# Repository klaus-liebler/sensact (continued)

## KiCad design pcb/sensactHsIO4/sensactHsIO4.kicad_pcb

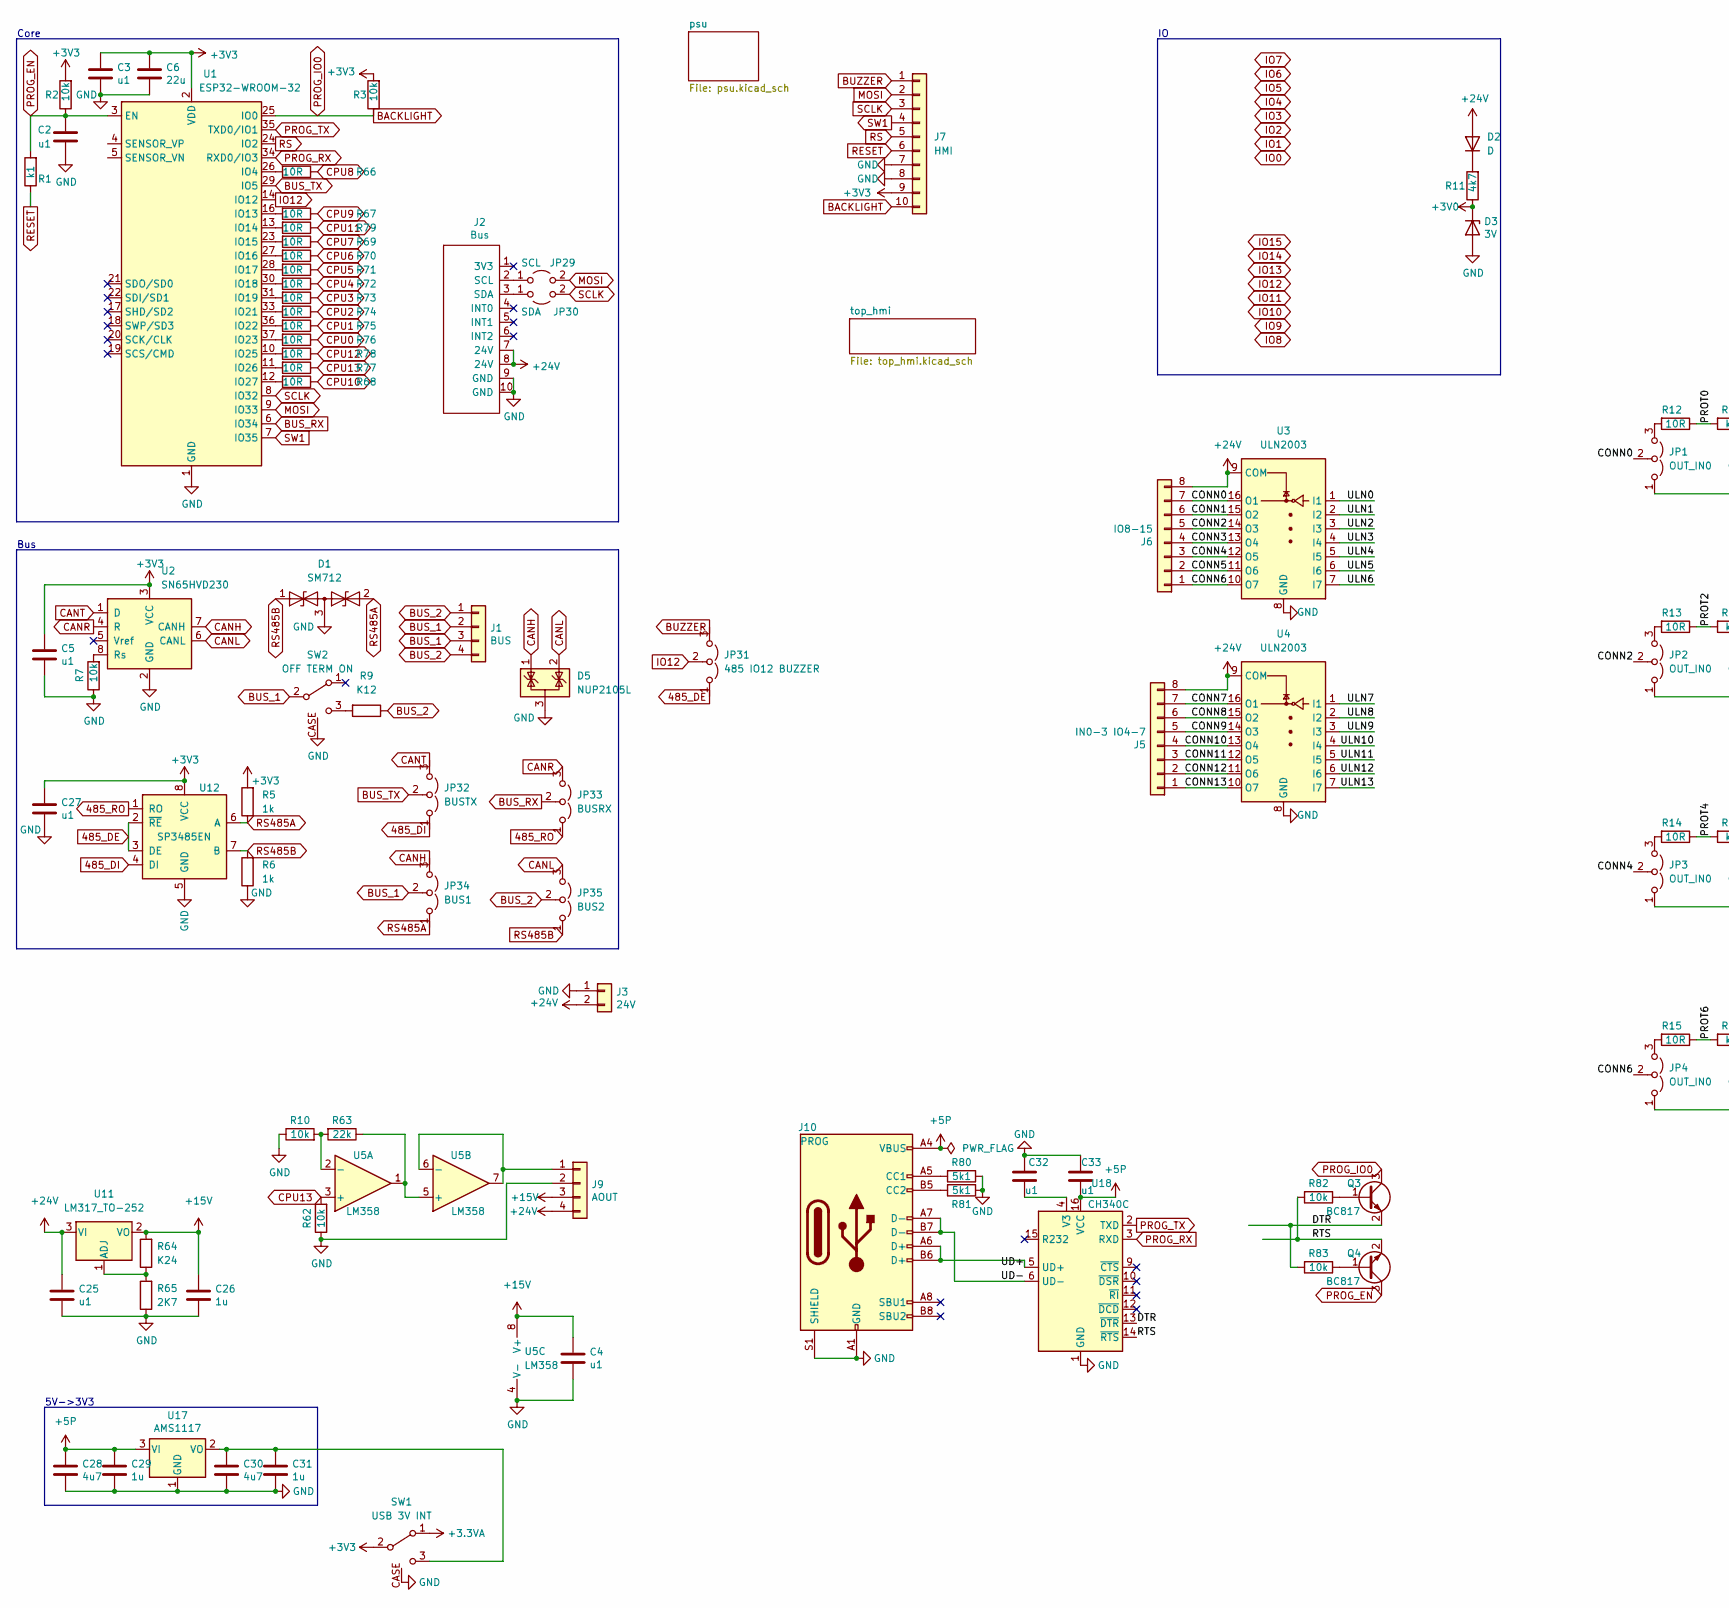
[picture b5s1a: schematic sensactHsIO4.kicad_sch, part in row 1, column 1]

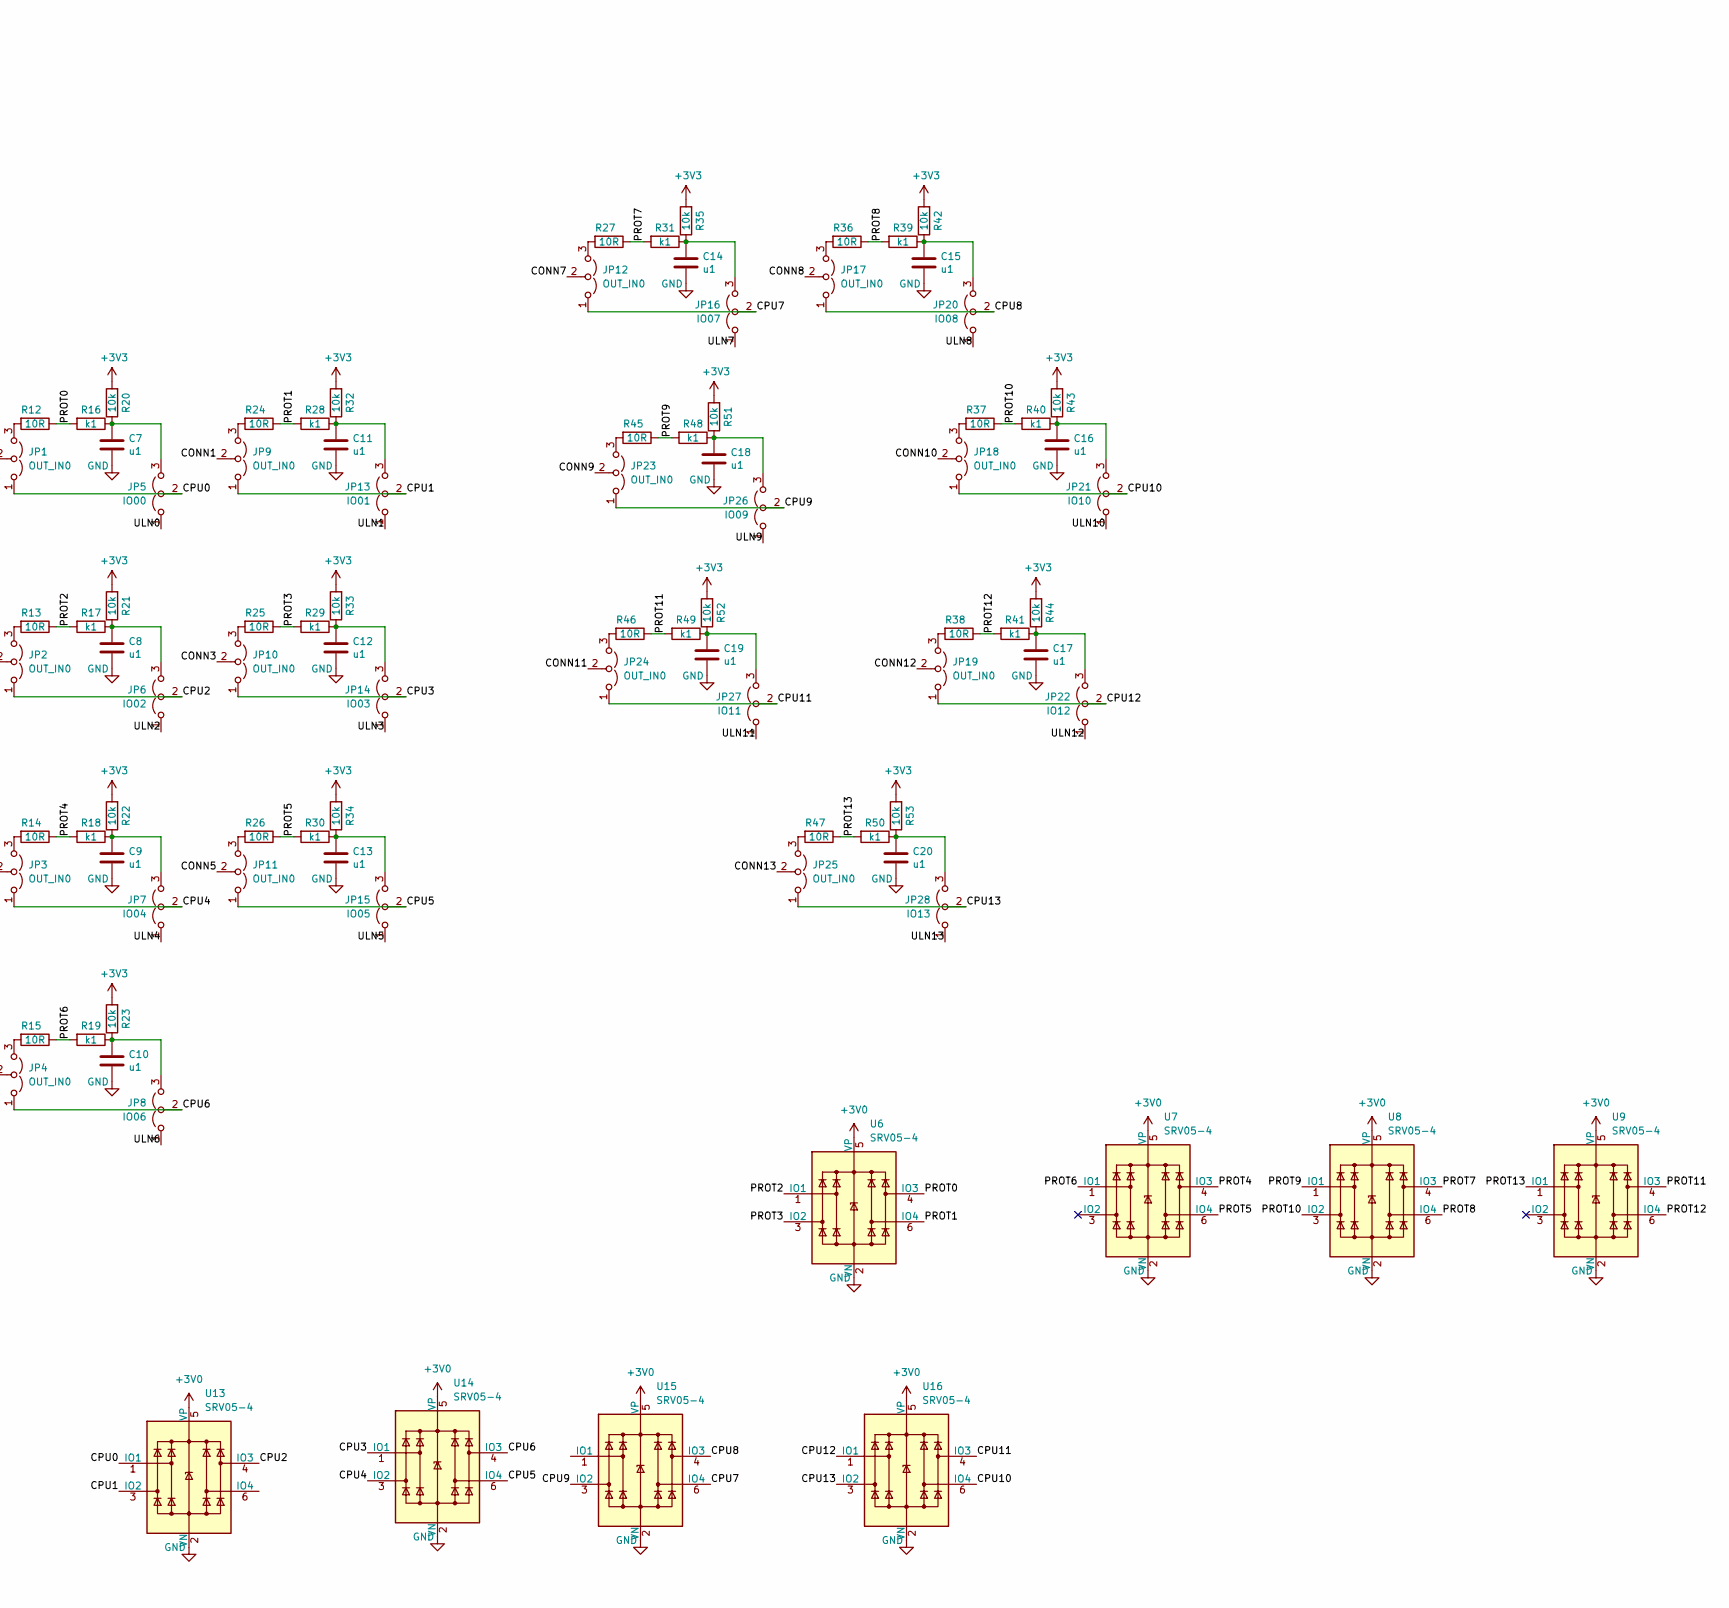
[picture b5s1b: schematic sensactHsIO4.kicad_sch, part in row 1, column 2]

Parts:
C2, C3, C7, C8, C9, C10, C11, C12, C13, C14, C15, C16, C17, C18, C19, C20: u1; C_0603_1608Metric
C4, C5, C25, C27, C32, C33: u1; C_0402_1005Metric
C6: 22u; C_0603_1608Metric
C26: 1u; C_0402_1005Metric
C28: 4u7; C_0603_1608Metric
C29: 1u; C_0603_1608Metric
C30: 4u7; C_0805_2012Metric_Pad1.18x1.45mm_HandSolder
C31: 1u; C_0805_2012Metric_Pad1.18x1.45mm_HandSolder
D1: SM712; SOT-23_Handsoldering
D2: D; D_SOD-123
D3: 3V; D_SOD-123
D5: NUP2105L; SOT-23_Handsoldering
J1: BUS; PhoenixContact_MC_1,5_4-G-3.5_1x04_P3.50mm_Horizontal
J2: Bus; IDC-Header_2x05_P2.54mm_Horizontal_tightCrtYd
J3: 24V; PhoenixContact_MC_1,5_2-G-3.5_1x02_P3.50mm_Horizontal
J5: IN0-3 IO4-7; PhoenixContact_MC_0,5_8-G-2.5_1x08_P2.50mm_Horizontal
J6: IO8-15; PhoenixContact_MC_0,5_8-G-2.5_1x08_P2.50mm_Horizontal
J7: HMI; Hirose_FH12-10S-0.5SH_1x10-1MP_P0.50mm_Horizontal
J9: AOUT; JST_XH_B4B-XH-A_1x04_P2.50mm_Vertical
J10: PROG; USB-C-HANBO-MC-307_C961709
JP1, JP2, JP3, JP4, JP9, JP10, JP11, JP12, JP17, JP18, JP19, JP23, JP24, JP25: OUT_IN0; SolderJumper-3_P1.3mm_Open_RoundedPad1.0x1.5mm
JP5: IO00; SolderJumper-3_P1.3mm_Open_RoundedPad1.0x1.5mm
JP6: IO02; SolderJumper-3_P1.3mm_Open_RoundedPad1.0x1.5mm
JP7: IO04; SolderJumper-3_P1.3mm_Open_RoundedPad1.0x1.5mm
JP8: IO06; SolderJumper-3_P1.3mm_Open_RoundedPad1.0x1.5mm
JP13: IO01; SolderJumper-3_P1.3mm_Open_RoundedPad1.0x1.5mm
JP14: IO03; SolderJumper-3_P1.3mm_Open_RoundedPad1.0x1.5mm
JP15: IO05; SolderJumper-3_P1.3mm_Open_RoundedPad1.0x1.5mm
JP16: IO07; SolderJumper-3_P1.3mm_Open_RoundedPad1.0x1.5mm
JP20: IO08; SolderJumper-3_P1.3mm_Open_RoundedPad1.0x1.5mm
JP21: IO10; SolderJumper-3_P1.3mm_Open_RoundedPad1.0x1.5mm
JP22: IO12; SolderJumper-3_P1.3mm_Open_RoundedPad1.0x1.5mm
JP26: IO09; SolderJumper-3_P1.3mm_Open_RoundedPad1.0x1.5mm
JP27: IO11; SolderJumper-3_P1.3mm_Open_RoundedPad1.0x1.5mm
JP28: IO13; SolderJumper-3_P1.3mm_Open_RoundedPad1.0x1.5mm
JP29: SCL; SolderJumper-2_P1.3mm_Open_RoundedPad1.0x1.5mm
JP30: SDA; SolderJumper-2_P1.3mm_Open_RoundedPad1.0x1.5mm
JP31: 485 IO12 BUZZER; SolderJumper-3_P1.3mm_Open_RoundedPad1.0x1.5mm
JP32: BUSTX; SolderJumper-3_P1.3mm_Open_RoundedPad1.0x1.5mm
JP33: BUSRX; SolderJumper-3_P1.3mm_Open_RoundedPad1.0x1.5mm
JP34: BUS1; SolderJumper-3_P1.3mm_Open_RoundedPad1.0x1.5mm
JP35: BUS2; SolderJumper-3_P1.3mm_Open_RoundedPad1.0x1.5mm
Q3, Q4: BC817; SOT-23
R1, R16, R17, R18, R19, R28, R29, R30, R31, R39, R40, R41, R48, R49, R50: k1; R_0603_1608Metric
R2, R7, R20, R21, R22, R23, R32, R33, R34, R35, R42, R43, R44, R51, R52, R53, R82, R83: 10k; R_0603_1608Metric
R3: 10k; R_0402_1005Metric_Pad0.72x0.64mm_HandSolder
R5, R6: 1k; R_0603_1608Metric
R9: K12; R_0603_1608Metric
R10, R62: 10k; R_0402_1005Metric
R11: 4k7; R_0603_1608Metric
R12, R13, R14, R15, R24, R25, R26, R27, R36, R37, R38, R45, R46, R47, R66, R67, R68, R69, R70, R71, R72, R73, R74, R75, R76, R77, R78, R79: 10R; R_0603_1608Metric
R63: 22k; R_0402_1005Metric
R64: K24; R_0603_1608Metric
R65: 2K7; R_0603_1608Metric
R80, R81: 5k1; R_0603_1608Metric
SW1: USB 3V INT; SW_SPDT_PCM12_handsolder
SW2: OFF TERM ON; SW_SPDT_PCM12_handsolder
U1: ESP32-WROOM-32
U2: SN65HVD230; SOIC-8_3.9x4.9mm_P1.27mm
U3, U4: ULN2003; SOP-16_3.9x9.9mm_P1.27mm
U5: LM358; SOIC-8_3.9x4.9mm_P1.27mm
U6, U7, U8, U9, U13, U14, U15, U16: SRV05-4; SOT-23-6-spezial
U11: LM317_TO-252; TO-252-2
U12: SP3485EN; SOIC-8_3.9x4.9mm_P1.27mm
U17: AMS1117; SOT-223-3_TabPin2_HANDSOLDER
U18: CH340C; SOIC-16_3.9x9.9mm_P1.27mm

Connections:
485_DE: JP31.1 (A), U12.2 (~RE), U12.3 (DE)
485_DI: JP32.1 (A), U12.4 (DI)
485_RO: JP33.1 (A), U12.1 (RO)
+3.3VA: SW1.1 (A); also elsewhere on the board
+3V0: D3.1 (K), R11.1, U6.5 (VP), U7.5 (VP), U8.5 (VP), U9.5 (VP), U13.5 (VP), U14.5 (VP), U15.5 (VP), U16.5 (VP)
+3V3: C3.1, C5.1, C6.1, C27.2, J7.9, R2.2, R3.2, R5.2, R20.2, R21.2, R22.2, R23.2, R32.2, R33.2, R34.2, R35.2, R42.2, R43.2, R44.2, R51.2, R52.2, R53.2, SW1.2 (B), U1.2 (VDD), U2.3 (VCC), U12.8 (VCC)
+5P: C28.2, C29.1, C33.1, J10.A4 (VBUS), J10.A9 (VBUS), J10.B4 (VBUS), J10.B9 (VBUS), U17.3 (VI), U18.16 (VCC)
+15V: C4.2, C26.2, J9.3, R64.2, U5.8 (V+), U11.2 (VO)
+24V: C25.2, D2.2 (A), J2.7 (24V), J2.8 (24V), J3.2, J5.8, J6.8, J9.4, U3.9 (COM), U4.9 (COM), U11.3 (VI); also elsewhere on the board
/CONN0: J6.7, JP1.2 (C), U3.16 (O1)
/CONN1: J6.6, JP9.2 (C), U3.15 (O2)
/CONN2: J6.5, JP2.2 (C), U3.14 (O3)
/CONN3: J6.4, JP10.2 (C), U3.13 (O4)
/CONN4: J6.3, JP3.2 (C), U3.12 (O5)
/CONN5: J6.2, JP11.2 (C), U3.11 (O6)
/CONN6: J6.1, JP4.2 (C), U3.10 (O7)
/CONN7: J5.7, JP12.2 (C), U4.16 (O1)
/CONN8: J5.6, JP17.2 (C), U4.15 (O2)
/CONN9: J5.5, JP23.2 (C), U4.14 (O3)
/CONN10: J5.4, JP18.2 (C), U4.13 (O4)
/CONN11: J5.3, JP24.2 (C), U4.12 (O5)
/CONN12: J5.2, JP19.2 (C), U4.11 (O6)
/CONN13: J5.1, JP25.2 (C), U4.10 (O7)
/DTR: Q3.2 (E), R83.2, U18.13 (~DTR)
/PROT0: R12.1, R16.2, U6.4 (IO3)
/PROT1: R24.1, R28.2, U6.6 (IO4)
/PROT2: R13.1, R17.2, U6.1 (IO1)
/PROT3: R25.1, R29.2, U6.3 (IO2)
/PROT4: R14.1, R18.2, U7.4 (IO3)
/PROT5: R26.1, R30.2, U7.6 (IO4)
/PROT6: R15.1, R19.2, U7.1 (IO1)
/PROT7: R27.1, R31.2, U8.4 (IO3)
/PROT8: R36.1, R39.2, U8.6 (IO4)
/PROT9: R45.1, R48.2, U8.1 (IO1)
/PROT10: R37.1, R40.2, U8.3 (IO2)
/PROT11: R46.1, R49.2, U9.4 (IO3)
/PROT12: R38.1, R41.2, U9.6 (IO4)
/PROT13: R47.1, R50.2, U9.1 (IO1)
/RTS: Q4.2 (E), R82.2, U18.14 (~RTS)
/UD+: J10.A6 (D+), J10.B6 (D+), U18.5 (UD+)
/UD-: J10.A7 (D-), J10.B7 (D-), U18.6 (UD-)
/ULN0: JP5.1 (A), U3.1 (I1)
/ULN1: JP13.1 (A), U3.2 (I2)
/ULN2: JP6.1 (A), U3.3 (I3)
/ULN3: JP14.1 (A), U3.4 (I4)
/ULN4: JP7.1 (A), U3.5 (I5)
/ULN5: JP15.1 (A), U3.6 (I6)
/ULN6: JP8.1 (A), U3.7 (I7)
/ULN7: JP16.1 (A), U4.1 (I1)
/ULN8: JP20.1 (A), U4.2 (I2)
/ULN9: JP26.1 (A), U4.3 (I3)
/ULN10: JP21.1 (A), U4.4 (I4)
/ULN11: JP27.1 (A), U4.5 (I5)
/ULN12: JP22.1 (A), U4.6 (I6)
/ULN13: JP28.1 (A), U4.7 (I7)
BACKLIGHT: J7.10, Q3.3 (C), R3.1, U1.25 (IO0)
BUS_1: J1.2, J1.3, JP34.2 (C), SW2.2 (B)
BUS_2: J1.1, J1.4, JP35.2 (C), R9.1
BUS_RX: JP33.2 (C), U1.6 (IO34)
BUS_TX: JP32.2 (C), U1.29 (IO5)
BUZZER: J7.1, JP31.3 (B)
CANH: D5.1 (K), JP34.3 (B), U2.7 (CANH)
CANL: D5.2 (K), JP35.3 (B), U2.6 (CANL)
CANR: JP33.3 (B), U2.4 (R)
CANT: JP32.3 (B), U2.1 (D)
CPU0: JP1.1 (A), JP5.2 (C), R76.1, U13.1 (IO1)
CPU1: JP9.1 (A), JP13.2 (C), R75.1, U13.3 (IO2)
CPU2: JP2.1 (A), JP6.2 (C), R74.1, U13.4 (IO3)
CPU3: JP10.1 (A), JP14.2 (C), R73.1, U14.1 (IO1)
CPU4: JP3.1 (A), JP7.2 (C), R72.1, U14.3 (IO2)
CPU5: JP11.1 (A), JP15.2 (C), R71.1, U14.6 (IO4)
CPU6: JP4.1 (A), JP8.2 (C), R70.1, U14.4 (IO3)
CPU7: JP12.1 (A), JP16.2 (C), R69.1, U15.6 (IO4)
CPU8: JP17.1 (A), JP20.2 (C), R66.1, U15.4 (IO3)
CPU9: JP23.1 (A), JP26.2 (C), R67.1, U15.3 (IO2)
CPU10: JP18.1 (A), JP21.2 (C), R68.1, U16.6 (IO4)
CPU11: JP24.1 (A), JP27.2 (C), R79.1, U16.4 (IO3)
CPU12: JP19.1 (A), JP22.2 (C), R78.1, U16.1 (IO1)
CPU13: JP25.1 (A), JP28.2 (C), R62.2, R77.1, U5.3 (+), U16.3 (IO2)
GND: C2.2, C3.2, C4.1, C5.2, C6.2, C7.2, C8.2, C9.2, C10.2, C11.2, C12.2, C13.2, C14.2, C15.2, C16.2, C17.2, C18.2, C19.2, C20.2, C25.1, C26.1, C27.1, C28.1, C29.2, C30.1, C31.2, C32.2, C33.2, D1.3 (common), D3.2 (A), D5.3 (A), J2.9 (GND), J2.10 (GND), J3.1, J7.7, J7.8, J9.2, J10.A1 (GND), J10.A12 (GND), J10.B1 (GND), J10.B12 (GND), J10.S1 (SHIELD), R6.1, R7.1, R10.1, R62.1, R65.1, R80.1, R81.1, SW1.CASE, SW2.CASE, U1.1 (GND), U1.15 (GND), U1.38 (GND), U1.39 (GND), U2.2 (GND), U3.8 (GND), U4.8 (GND), U5.4 (V-), U6.2 (VN), U7.2 (VN), U8.2 (VN), U9.2 (VN), U12.5 (GND), U13.2 (VN), U14.2 (VN), U15.2 (VN), U16.2 (VN), U17.1 (GND), U18.1 (GND); also elsewhere on the board
IO12: JP31.2 (C), U1.14 (IO12)
MOSI: J7.2, JP29.2 (B), U1.9 (IO33)
unnamed: C7.1, JP5.3 (B), R16.1, R20.1
unnamed: C8.1, JP6.3 (B), R17.1, R21.1
unnamed: C9.1, JP7.3 (B), R18.1, R22.1
unnamed: C10.1, JP8.3 (B), R19.1, R23.1
unnamed: C11.1, JP13.3 (B), R28.1, R32.1
unnamed: C12.1, JP14.3 (B), R29.1, R33.1
unnamed: C13.1, JP15.3 (B), R30.1, R34.1
unnamed: C14.1, JP16.3 (B), R31.1, R35.1
unnamed: C15.1, JP20.3 (B), R39.1, R42.1
unnamed: C16.1, JP21.3 (B), R40.1, R43.1
unnamed: C17.1, JP22.3 (B), R41.1, R44.1
unnamed: C18.1, JP26.3 (B), R48.1, R51.1
unnamed: C19.1, JP27.3 (B), R49.1, R52.1
unnamed: C20.1, JP28.3 (B), R50.1, R53.1
unnamed: C30.2, C31.1, SW1.3 (C), U17.2 (VO)
unnamed: C32.1, U18.4 (V3)
unnamed: D2.1 (K), R11.2
unnamed: J2.2 (SCL), JP29.1 (A)
unnamed: J2.3 (SDA), JP30.1 (A)
unnamed: J9.1, U5.6 (-), U5.7
unnamed: J10.A5 (CC1), R80.2
unnamed: J10.B5 (CC2), R81.2
unnamed: JP1.3 (B), R12.2
unnamed: JP2.3 (B), R13.2
unnamed: JP3.3 (B), R14.2
unnamed: JP4.3 (B), R15.2
unnamed: JP9.3 (B), R24.2
unnamed: JP10.3 (B), R25.2
unnamed: JP11.3 (B), R26.2
unnamed: JP12.3 (B), R27.2
unnamed: JP17.3 (B), R36.2
unnamed: JP18.3 (B), R37.2
unnamed: JP19.3 (B), R38.2
unnamed: JP23.3 (B), R45.2
unnamed: JP24.3 (B), R46.2
unnamed: JP25.3 (B), R47.2
unnamed: Q3.1 (B), R82.1
unnamed: Q4.1 (B), R83.1
unnamed: R7.2, U2.8 (Rs)
unnamed: R9.2, SW2.3 (C)
unnamed: R10.2, R63.2, U5.2 (-)
unnamed: R63.1, U5.1, U5.5 (+)
unnamed: R64.1, R65.2, U11.1 (ADJ)
unnamed: R66.2, U1.26 (IO4)
unnamed: R67.2, U1.16 (IO13)
unnamed: R68.2, U1.12 (IO27)
unnamed: R69.2, U1.23 (IO15)
unnamed: R70.2, U1.27 (IO16)
unnamed: R71.2, U1.28 (IO17)
unnamed: R72.2, U1.30 (IO18)
unnamed: R73.2, U1.31 (IO19)
unnamed: R74.2, U1.33 (IO21)
unnamed: R75.2, U1.36 (IO22)
unnamed: R76.2, U1.37 (IO23)
unnamed: R77.2, U1.11 (IO26)
unnamed: R78.2, U1.10 (IO25)
unnamed: R79.2, U1.13 (IO14)
PROG_EN: C2.1, Q4.3 (C), R1.2, R2.1, U1.3 (EN)
PROG_RX: U1.34 (RXD0/IO3), U18.3 (RXD)
PROG_TX: U1.35 (TXD0/IO1), U18.2 (TXD)
RESET: J7.6, R1.1
RS: J7.5, U1.24 (IO2)
RS485A: D1.2 (A2), JP34.1 (A), R5.1, U12.6 (A)
RS485B: D1.1 (A1), JP35.1 (A), R6.2, U12.7 (B)
SCLK: J7.3, JP30.2 (B), U1.8 (IO32)
SW1: J7.4, U1.7 (IO35)

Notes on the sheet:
Core
5V->3V3
Bus

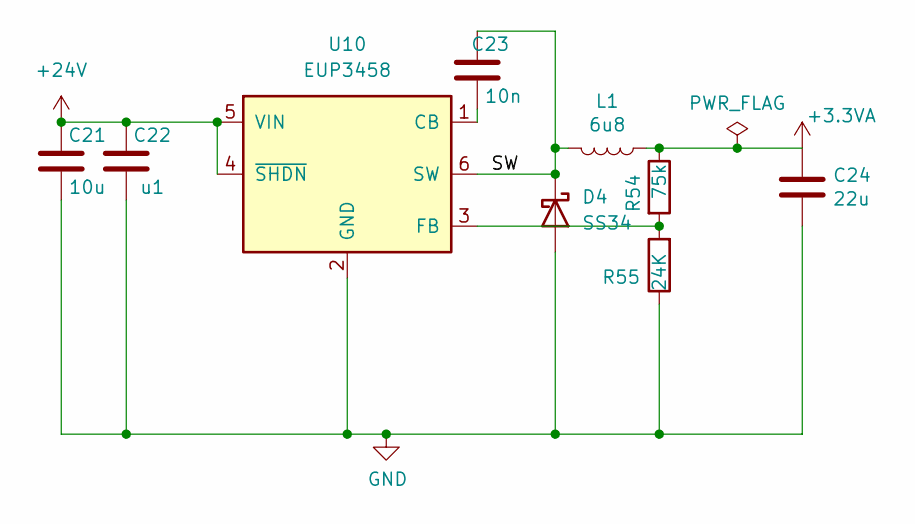
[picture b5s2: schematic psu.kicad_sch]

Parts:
C21: 10u; C_1206_3216Metric
C22: u1; C_0603_1608Metric
C23: 10n; C_0603_1608Metric
C24: 22u; C_0603_1608Metric
D4: SS34; D_SMA
L1: 6u8; L_Abracon_ASPI-0630LR
R54: 75k; R_0603_1608Metric
R55: 24K; R_0603_1608Metric
U10: EUP3458; SOT-23-6

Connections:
+3.3VA: C24.1, L1.1, R54.1; also elsewhere on the board
+24V: C21.2, C22.2, U10.4 (~SHDN), U10.5 (VIN); also elsewhere on the board
/psu/SW: C23.2, D4.1 (K), L1.2, U10.6 (SW)
GND: C21.1, C22.1, C24.2, D4.2 (A), R55.1, U10.2 (GND); also elsewhere on the board
unnamed: C23.1, U10.1 (CB)
unnamed: R54.2, R55.2, U10.3 (FB)

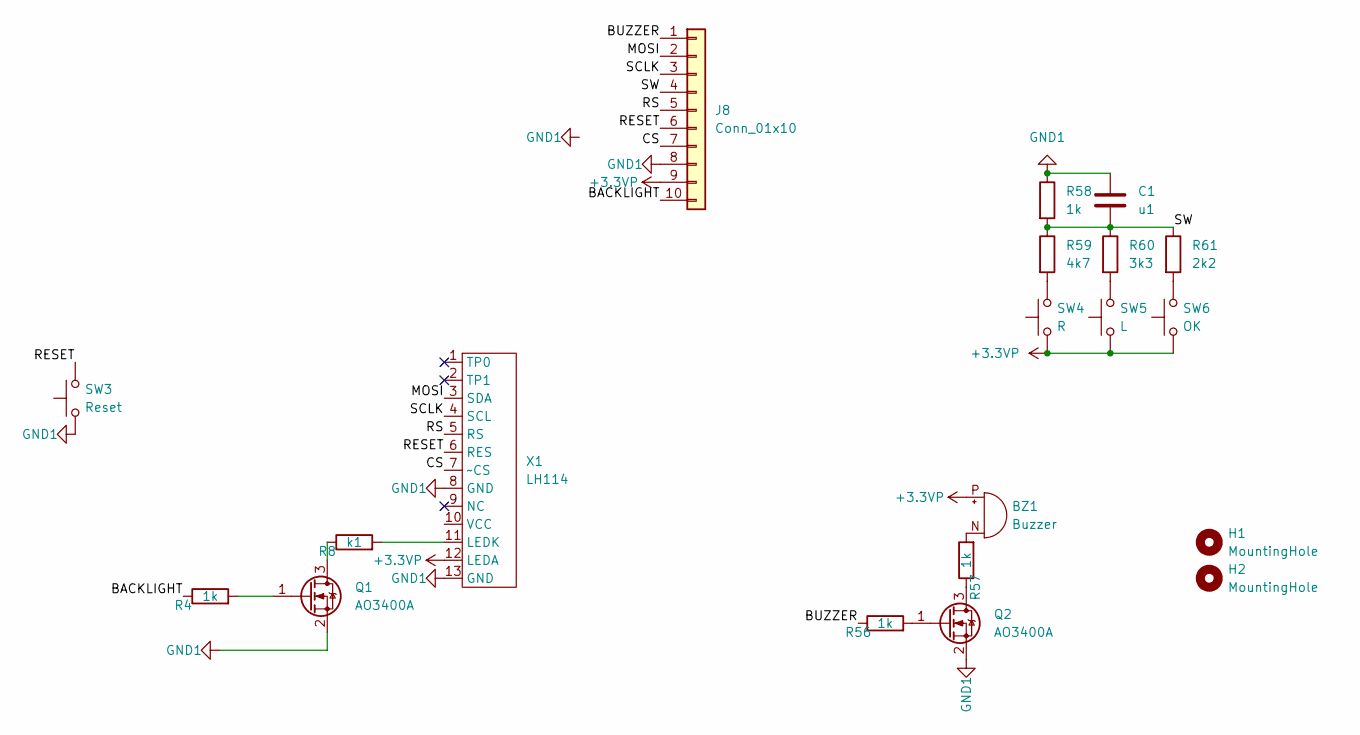
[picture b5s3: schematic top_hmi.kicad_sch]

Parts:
BZ1: Buzzer; XDCR_CMT-7525-80-SMT-TR
C1: u1; C_0402_1005Metric
H1, H2: MountingHole; MountingHole_2mm
J8: Conn_01x10; Hirose_FH12-10S-0.5SH_1x10-1MP_P0.50mm_Horizontal
Q1, Q2: AO3400A; SOT-23
R4, R56, R58: 1k; R_0402_1005Metric
R8: k1; R_0603_1608Metric
R57: 1k; R_0603_1608Metric
R59: 4k7; R_0402_1005Metric
R60: 3k3; R_0402_1005Metric
R61: 2k2; R_0402_1005Metric
SW3: Reset; Button_2x4x3,5_handsolder
SW4: R; Button_SMD_4,5x4,5
SW5: L; Button_SMD_4,5x4,5
SW6: OK; Button_SMD_4,5x4,5
X1: LH114; FP-114 13pol

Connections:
+3.3VP: BZ1.P (-), J8.9, SW4.1, SW5.1, SW6.1, X1.12 (LEDA)
/top_hmi/BACKLIGHT: J8.10, R4.1
/top_hmi/BUZZER: J8.1, R56.1
/top_hmi/CS: J8.7, X1.7 (~CS)
/top_hmi/MOSI: J8.2, X1.3 (SDA)
/top_hmi/RESET: J8.6, SW3.1, X1.6 (RES)
/top_hmi/RS: J8.5, X1.5 (RS)
/top_hmi/SCLK: J8.3, X1.4 (SCL)
/top_hmi/SW: C1.2, J8.4, R58.2, R59.1, R60.1, R61.1
GND1: C1.1, J8.8, Q1.2 (S), Q2.2 (S), R58.1, SW3.2, X1.8 (GND), X1.13 (GND)
unnamed: BZ1.N (+), R57.2
unnamed: Q1.1 (G), R4.2
unnamed: Q1.3 (D), R8.1
unnamed: Q2.1 (G), R56.2
unnamed: Q2.3 (D), R57.1
unnamed: R8.2, X1.11 (LEDK)
unnamed: R59.2, SW4.2
unnamed: R60.2, SW5.2
unnamed: R61.2, SW6.2

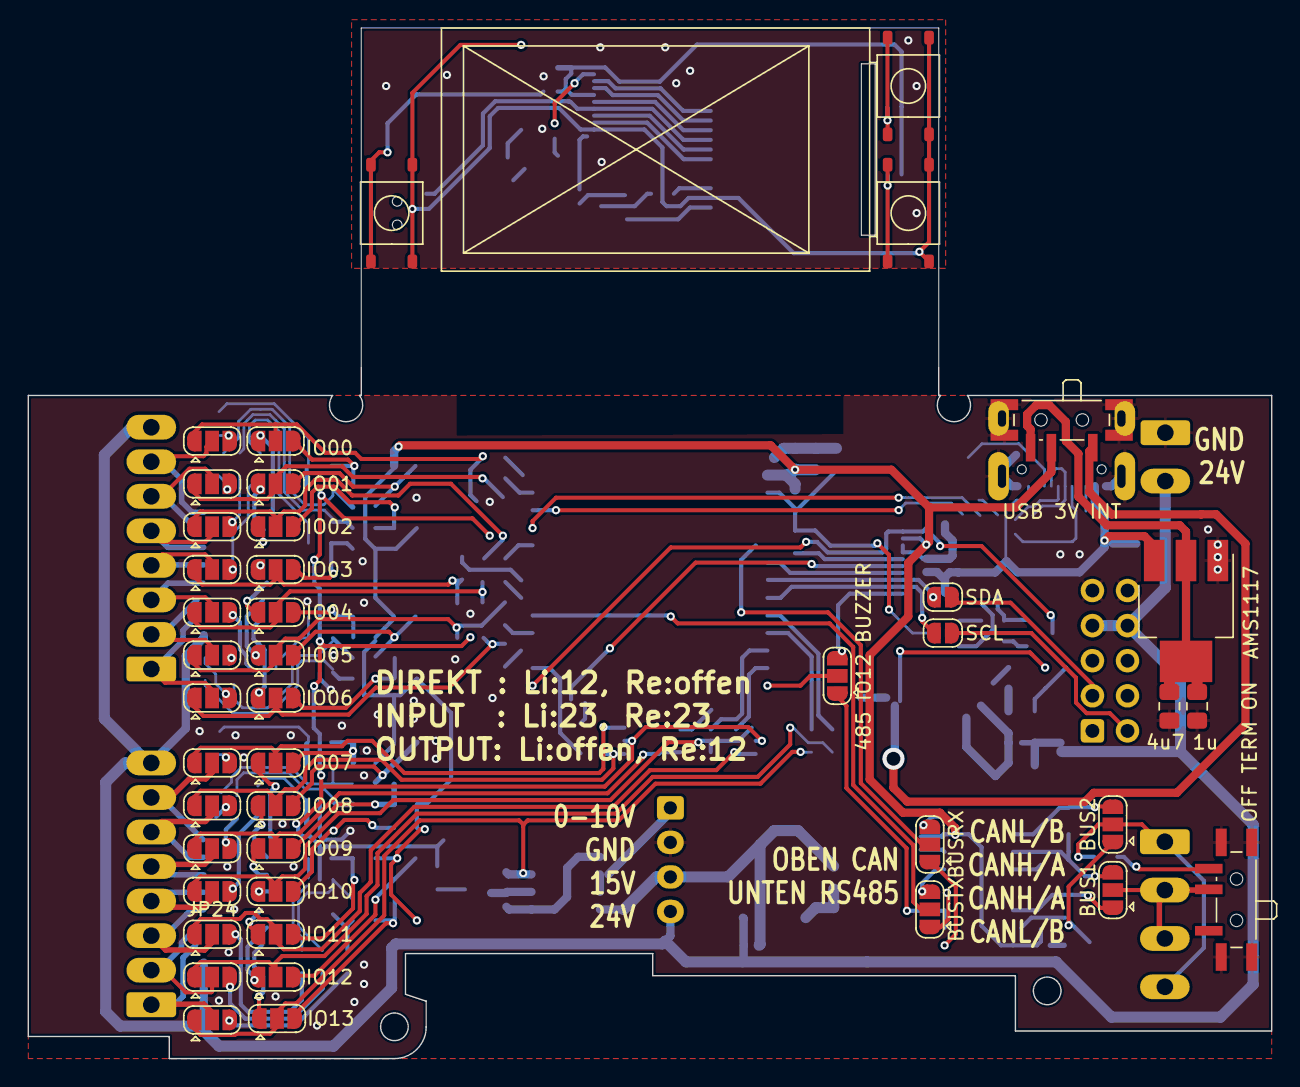
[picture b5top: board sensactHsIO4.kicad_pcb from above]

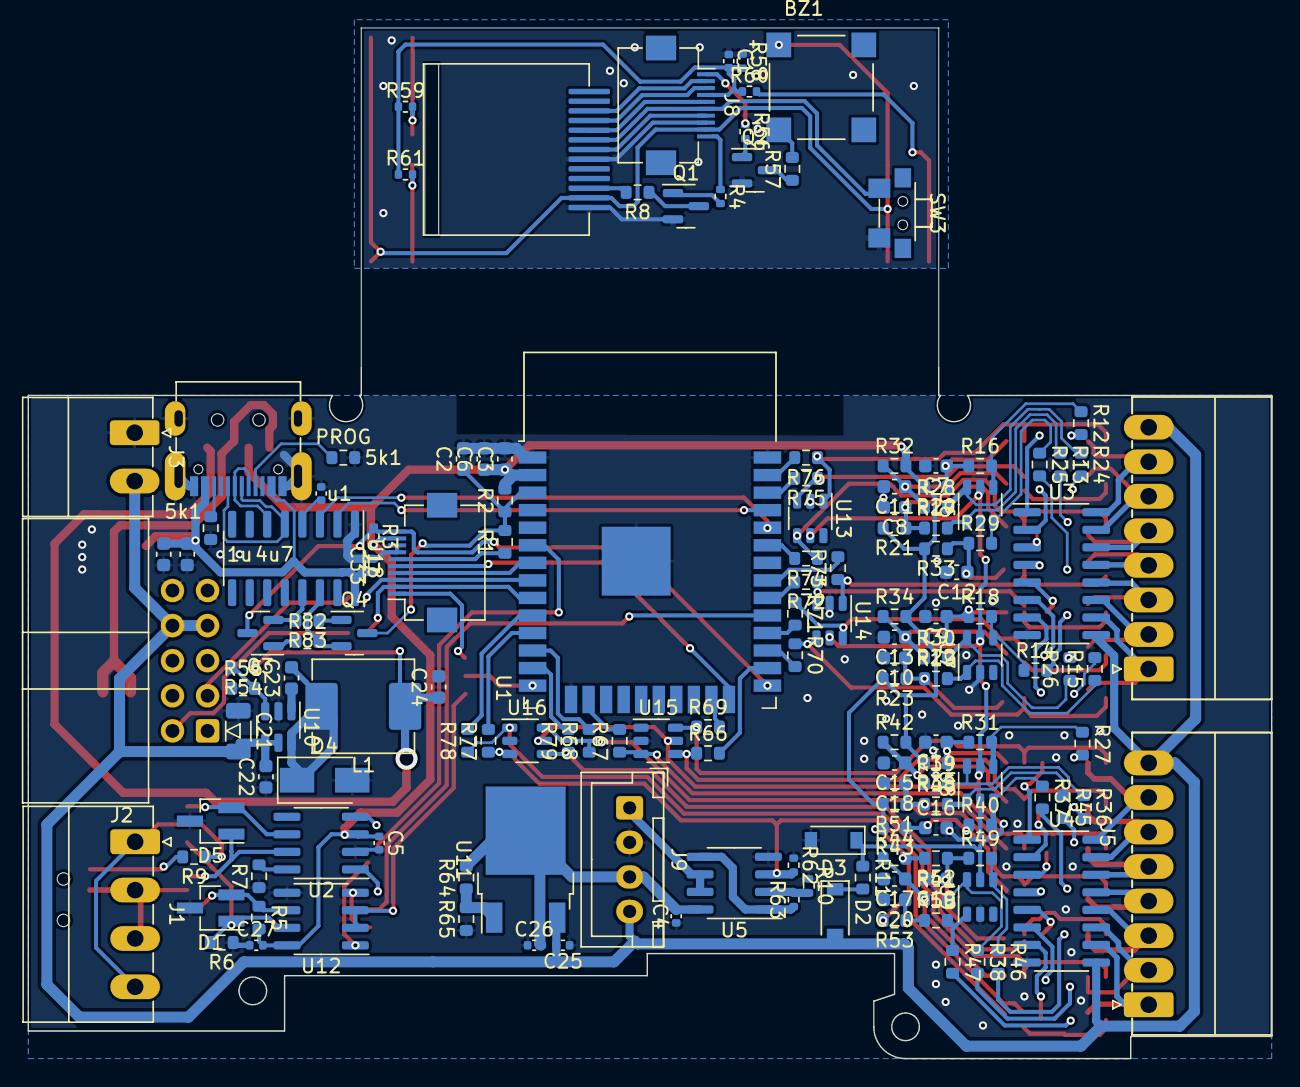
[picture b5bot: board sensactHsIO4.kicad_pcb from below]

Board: 2 copper layers, 90.0 x 74.6 mm, 198 parts (152 on the bottom side), 170 nets.

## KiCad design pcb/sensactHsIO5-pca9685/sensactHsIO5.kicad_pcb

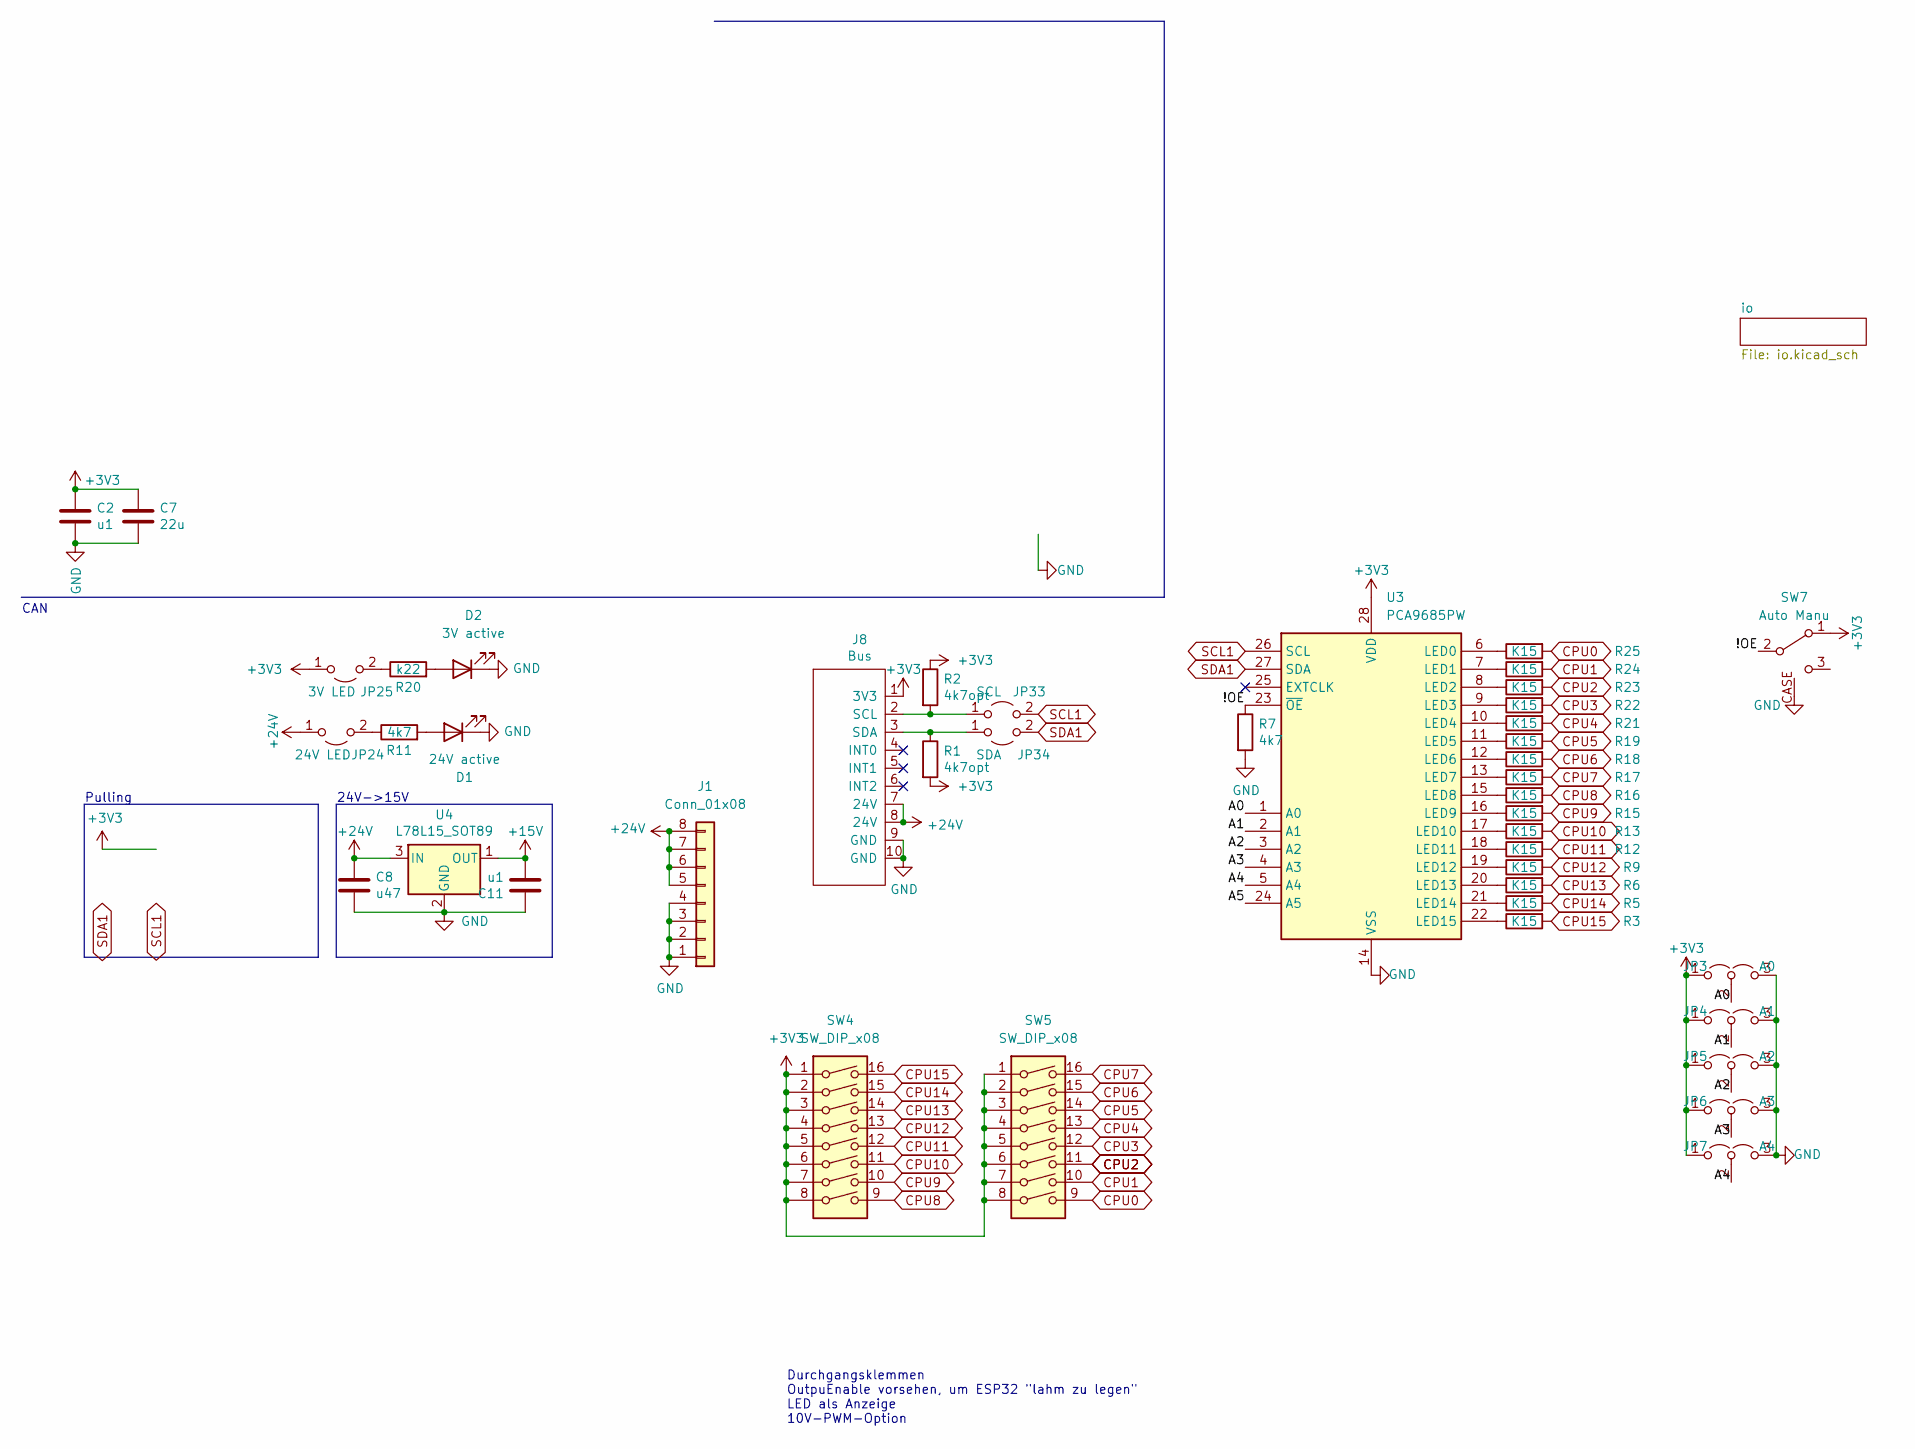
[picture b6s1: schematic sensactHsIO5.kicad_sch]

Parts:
C2, C11: u1; C_0402_1005Metric
C7: 22u; C_0603_1608Metric
C8: u47; C_0805_2012Metric
D1: 24V active; LED_1606
D2: 3V active; LED_1606
J1: Conn_01x08; PhoenixContact_MC_0,5_8-G-2.5_1x08_P2.50mm_Horizontal
J8: Bus; IDC-Header_2x05_P2.54mm_Horizontal_tightCrtYd
JP3: A0; SolderJumper-3_P1.3mm_Open_RoundedPad1.0x1.5mm_NumberLabels
JP4: A1; SolderJumper-3_P1.3mm_Open_RoundedPad1.0x1.5mm_NumberLabels
JP5: A2; SolderJumper-3_P1.3mm_Open_RoundedPad1.0x1.5mm_NumberLabels
JP6: A3; SolderJumper-3_P1.3mm_Open_RoundedPad1.0x1.5mm_NumberLabels
JP7: A4; SolderJumper-3_P1.3mm_Open_RoundedPad1.0x1.5mm_NumberLabels
JP24: 24V LED; SolderJumper-2_P1.3mm_Open_RoundedPad1.0x1.5mm
JP25: 3V LED; SolderJumper-2_P1.3mm_Open_RoundedPad1.0x1.5mm
JP33: SCL; SolderJumper-2_P1.3mm_Bridged2Bar_RoundedPad1.0x1.5mm
JP34: SDA; SolderJumper-2_P1.3mm_Bridged2Bar_RoundedPad1.0x1.5mm
R1, R2: 4k7opt; R_0402_1005Metric
R3, R5, R6, R9, R12, R13, R15, R16, R17, R18, R19, R21, R22, R23, R24, R25: K15; R_0805_2012Metric
R7: 4k7; R_0402_1005Metric
R11: 4k7; R_1206_3216Metric
R20: k22; R_0402_1005Metric
SW4, SW5: SW_DIP_x08; SW_DIP_SPSTx08_Piano
SW7: Auto Manu; SW_SPDT_PCM12_handsolder
U3: PCA9685PW; TSSOP-28_4.4x9.7mm_Pitch0.65mm_handsolder
U4: L78L15_SOT89; SOT-89-3_Handsoldering

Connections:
+3V3: C2.1, C7.1, J8.1 (3V3), JP3.1 (A), JP4.1 (A), JP5.1 (A), JP6.1 (A), JP7.1 (A), JP25.1 (A), R1.2, R2.1, SW4.1, SW4.2, SW4.3, SW4.4, SW4.5, SW4.6, SW4.7, SW4.8, SW5.1, SW5.2, SW5.3, SW5.4, SW5.5, SW5.6, SW5.7, SW5.8, SW7.1 (A), U3.28 (VDD)
+15V: C11.2, U4.1 (OUT); also elsewhere on the board
/!OE: R7.1, SW7.2 (B), U3.23 (~OE)
/A0: JP3.2 (C), U3.1 (A0)
/A1: JP4.2 (C), U3.2 (A1)
/A2: JP5.2 (C), U3.3 (A2)
/A3: JP6.2 (C), U3.4 (A3)
/A4: JP7.2 (C), U3.5 (A4)
/A5: U3.24 (A5)
CPU0: R25.2, SW5.9; also elsewhere on the board
CPU1: R24.2, SW5.10; also elsewhere on the board
CPU2: R23.2, SW5.11; also elsewhere on the board
CPU3: R22.2, SW5.12; also elsewhere on the board
CPU4: R21.2, SW5.13; also elsewhere on the board
CPU5: R19.2, SW5.14; also elsewhere on the board
CPU6: R18.2, SW5.15; also elsewhere on the board
CPU7: R17.2, SW5.16; also elsewhere on the board
CPU8: R16.2, SW4.9; also elsewhere on the board
CPU9: R15.2, SW4.10; also elsewhere on the board
CPU10: R13.2, SW4.11; also elsewhere on the board
CPU11: R12.2, SW4.12; also elsewhere on the board
CPU12: R9.2, SW4.13; also elsewhere on the board
CPU13: R6.2, SW4.14; also elsewhere on the board
CPU14: R5.2, SW4.15; also elsewhere on the board
CPU15: R3.2, SW4.16; also elsewhere on the board
unnamed: D1.2 (A), R11.2
unnamed: D2.2 (A), R20.2
unnamed: J8.2 (SCL), JP33.1 (A), R2.2
unnamed: J8.3 (SDA), JP34.1 (A), R1.1
unnamed: JP24.2 (B), R11.1
unnamed: JP25.2 (B), R20.1
unnamed: R25.1, U3.6 (LED0)
unnamed: R24.1, U3.7 (LED1)
unnamed: R23.1, U3.8 (LED2)
unnamed: R22.1, U3.9 (LED3)
unnamed: R21.1, U3.10 (LED4)
unnamed: R19.1, U3.11 (LED5)
unnamed: R18.1, U3.12 (LED6)
unnamed: R17.1, U3.13 (LED7)
unnamed: R16.1, U3.15 (LED8)
unnamed: R15.1, U3.16 (LED9)
unnamed: R13.1, U3.17 (LED10)
unnamed: R12.1, U3.18 (LED11)
unnamed: R9.1, U3.19 (LED12)
unnamed: R6.1, U3.20 (LED13)
unnamed: R5.1, U3.21 (LED14)
unnamed: R3.1, U3.22 (LED15)
SCL1: JP33.2 (B), U3.26 (SCL)
SDA1: JP34.2 (B), U3.27 (SDA)

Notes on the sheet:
Pulling
Durchgangsklemmen OutpuEnable vorsehen, um ESP32 "lahm zu legen" LED als Anzeige 10V-PWM-Option
CAN
24V->15V
